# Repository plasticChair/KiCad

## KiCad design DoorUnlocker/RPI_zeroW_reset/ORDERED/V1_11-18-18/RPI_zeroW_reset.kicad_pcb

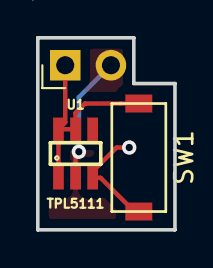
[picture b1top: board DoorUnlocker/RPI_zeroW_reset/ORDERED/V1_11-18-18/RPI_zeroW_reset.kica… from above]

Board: 2 copper layers, 7.6 x 10.7 mm, 4 parts (1 on the bottom side), 3 nets.

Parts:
J1: Conn_01x02; PinHeader_1x02_P2.54mm_Horizontal
R1: R; 1206
SW1: Button; Tact_SMD_Switch
U1: TPL5111; SOT-23-6

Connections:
unnamed: J1.1, SW1.2, U1.1, U1.5, U1.6
unnamed: J1.2, R1.1, U1.2
unnamed: R1.2, SW1.1, U1.3

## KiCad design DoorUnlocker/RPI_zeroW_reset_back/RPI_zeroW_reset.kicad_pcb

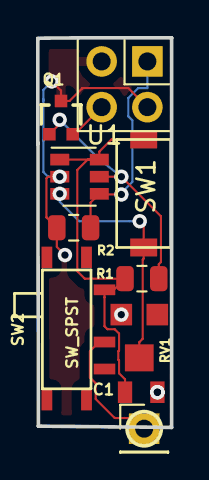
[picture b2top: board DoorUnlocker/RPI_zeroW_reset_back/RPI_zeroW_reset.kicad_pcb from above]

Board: 2 copper layers, 7.4 x 21.7 mm, 10 parts (0 on the bottom side), 7 nets.

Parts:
C1: C_Small; 0805
J1: RPI_Conn; PinHeader_2x02_P2.54mm_Vertical
J2: Conn_01x01; PinHeader_1x01_P2.54mm_Vertical
Q1: BSS83P; SOT323
R1, R2: R; R_0805_2012Metric
RV1: R_POT; Bourns_TC33X-2
SW1: SW_Push; Tact_SMD_Switch
SW2: SW_SPST; SWITCH_SPDT_PTH
U1: TPL5111; SOT-23-6

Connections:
+5V: C1.2, R1.2, SW1.2, SW2.1, U1.1, U1.6
/GPIO26: J1.1, R2.2, U1.4
/RUN: J1.4, Q1.2
GND: C1.1, J1.2, J1.3, Q1.3, R2.1, RV1.2, U1.2
unnamed: J2.1, SW2.2
unnamed: Q1.1, R1.1, U1.5
unnamed: RV1.1, SW1.1, U1.3

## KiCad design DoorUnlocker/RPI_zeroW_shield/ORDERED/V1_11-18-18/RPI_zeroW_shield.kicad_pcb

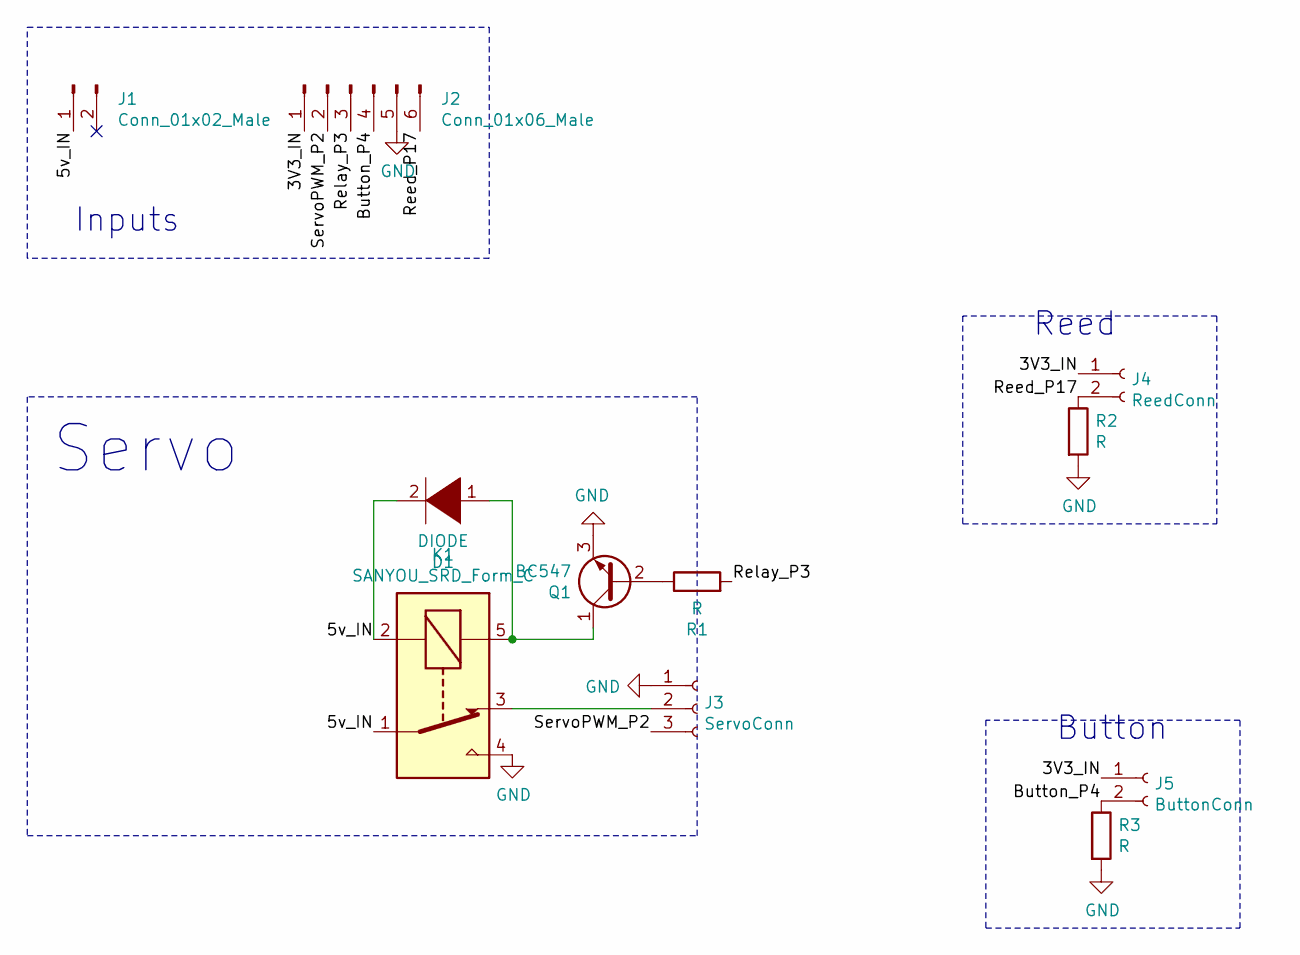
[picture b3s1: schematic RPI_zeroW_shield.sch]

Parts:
D1: DIODE; D_SOD-323_HandSoldering
J1: Conn_01x02_Male; PinHeader_1x02_P2.54mm_Horizontal
J2: Conn_01x06_Male; PinHeader_1x06_P2.54mm_Horizontal
J3: ServoConn; Pin_Header_1x03_Pitch2.54mm
J4: ReedConn; PinHeader_1x02_P2.54mm_Horizontal
J5: ButtonConn; PinHeader_1x02_P2.54mm_Horizontal
K1: SANYOU_SRD_Form_C; Relay_SPDT_SANYOU_SRD_Series_Form_C
Q1: BC547; TO-92_Inline
R1, R2, R3: R; 1206

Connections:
/3V3_IN: J2.1, J4.1, J5.1
/5v_IN: D1.2 (A), J1.1, K1.1, K1.2
/Button_P4: J2.4, J5.2, R3.1
/Reed_P17: J2.6, J4.2, R2.1
/Relay_P3: J2.3, R1.2
/ServoPWM_P2: J2.2, J3.3
GND: J2.5, J3.1, K1.4, Q1.3 (E), R2.2, R3.2
unnamed: D1.1 (K), K1.5, Q1.1 (C)
unnamed: J3.2, K1.3
unnamed: Q1.2 (B), R1.1

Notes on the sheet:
Servo
Button
Inputs
Reed

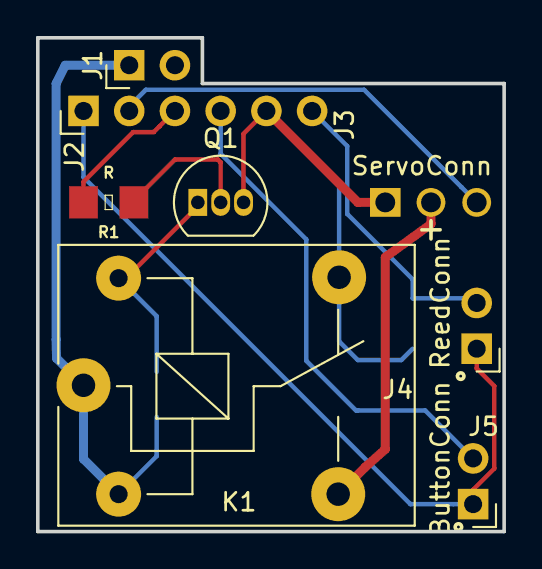
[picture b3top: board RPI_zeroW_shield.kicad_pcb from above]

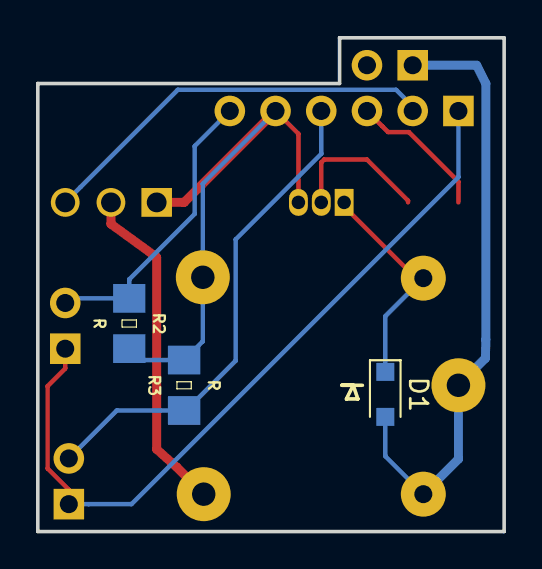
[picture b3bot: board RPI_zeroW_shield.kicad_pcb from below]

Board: 2 copper layers, 25.9 x 27.4 mm, 11 parts (3 on the bottom side), 10 nets.

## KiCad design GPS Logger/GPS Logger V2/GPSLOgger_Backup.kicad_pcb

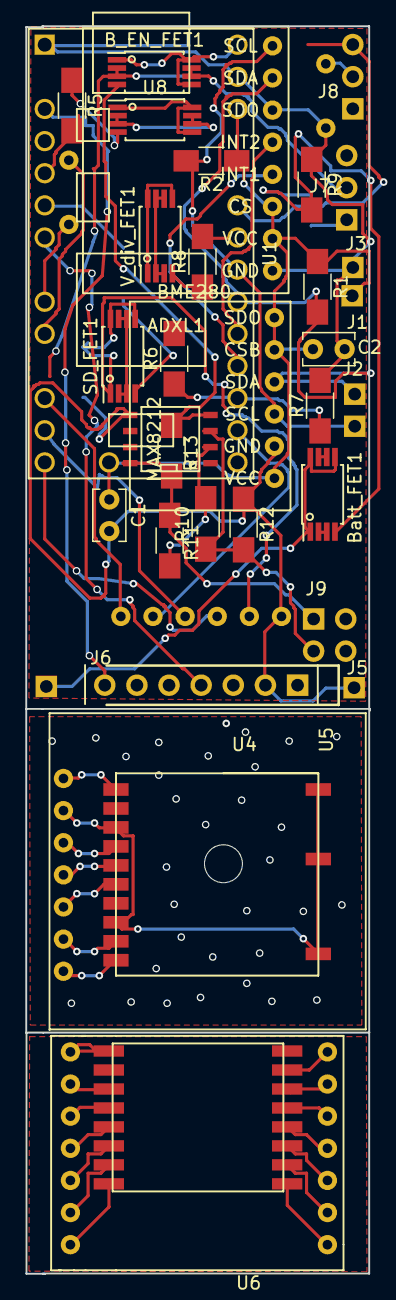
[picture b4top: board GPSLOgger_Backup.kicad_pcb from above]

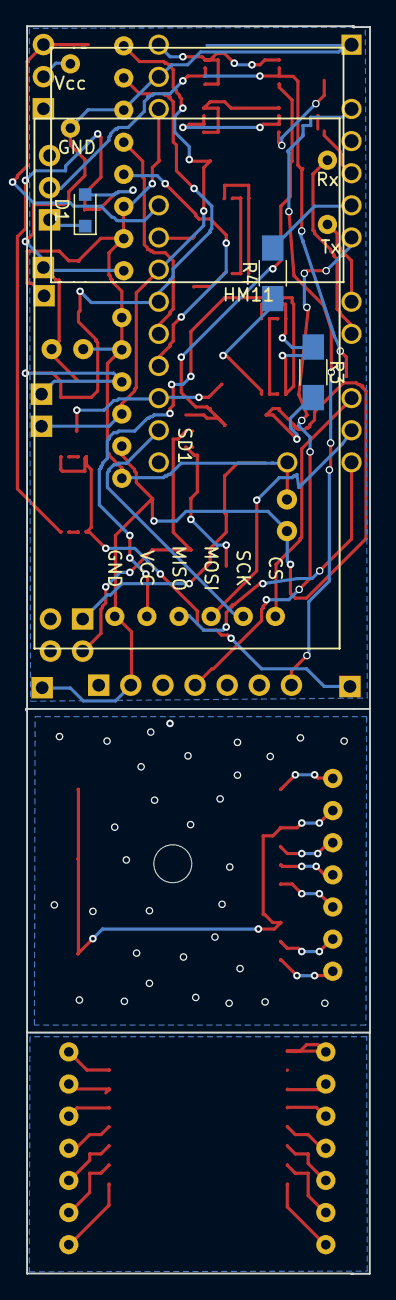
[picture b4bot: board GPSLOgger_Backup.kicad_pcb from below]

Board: 2 copper layers, 27.1 x 79.6 mm, 39 parts (5 on the bottom side), 33 nets.

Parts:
ADXL1: ADXL345_Breakout
BME280: BME280_Breakout
B_EN_FET1: Batt_En_FET; TSSOP-8_4.4x3mm_Pitch0.65mm_custom
Batt_FET1: Batt_EnFDW254p; TSSOP-8_4.4x3mm_Pitch0.65mm_custom
C1, C2: C; C_Rect_L4.0mm_W2.5mm_P2.50mm
D1: D_Schottky; D_SOD-323_HandSoldering
HM11: HM-11_BreakConns
J1: 3.3V; Pin_Header_1x01_Pitch2.54mm
J2: SDA; Pin_Header_1x01_Pitch2.54mm
J3: GND; Pin_Header_1x01_Pitch2.54mm
J4: SDL; Pin_Header_1x01_Pitch2.54mm
J5: -Batt; Pin_Header_1x01_Pitch2.54mm
J6: +Batt; Pin_Header_1x01_Pitch2.54mm
J7: BattSwitch; Pin_Header_1x03_Pitch2.54mm
J8: HM11Switch; Pin_Header_1x03_Pitch2.54mm
J9: CONN_02X02; Pin_Header_Angled_2x02_Pitch2.54mm
MAX8212: MAX8212; SOIC-8-N
R1, R2, R6, R7: R; R_1206_HandSoldering
R3, R4, R5: R_Small; R_1206_HandSoldering
R8: 10k; R_1206_HandSoldering
R9: 100k; R_1206_HandSoldering
R10, R11, R12, R13: 1M; R_1206_HandSoldering
SD1: SDCard_Breakout
SD_FET1: SD_EN_FDW254p; TSSOP-8_4.4x3mm_Pitch0.65mm_custom
U1: Teensy-LC; Teensy_LC
U4: GNS601_Breakout
U5: GPS Connector; Pin_Header_Angled_1x07_Pitch2.54mm
U6: HM-11; HM-11_Breakout
U8: GPS_FDW254p; TSSOP-8_4.4x3mm_Pitch0.65mm_custom
V_div_FET1: VDiv_FDW254p; TSSOP-8_4.4x3mm_Pitch0.65mm_custom

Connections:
+3V3: ADXL1.2, ADXL1.3, BME280.1, BME280.2, BME280.6, C1.1, C2.1, J1.1, R1.1, R2.1, U1.16, U1.31
GND: ADXL1.1, ADXL1.6, BME280.5, C1.2, C2.2, HM11.12, J3.1, J5.1, MAX8212.5, R3.2, R7.2, R9.1, R12.1, SD1.1, U1.1, U5.2
unnamed: ADXL1.4, U1.23
unnamed: ADXL1.5, U1.24
unnamed: ADXL1.7, BME280.3, J2.1, R1.2, U1.25
unnamed: ADXL1.8, BME280.4, J4.1, R2.2, U1.26
unnamed: B_EN_FET1.1, U1.33
unnamed: B_EN_FET1.2, J7.2, J9.1, MAX8212.8, R11.2, R13.2
unnamed: B_EN_FET1.4, MAX8212.4, R13.1
unnamed: Batt_FET1.1, J6.1
unnamed: Batt_FET1.2, D1.1, J7.1
unnamed: Batt_FET1.4, D1.2, R9.2
unnamed: HM11.2, U1.9
unnamed: HM11.4, U1.10
unnamed: HM11.9, J8.2
unnamed: J8.3, U1.28
unnamed: J9.3, MAX8212.3, R10.1, R12.2
unnamed: MAX8212.2, R10.2, R11.1
unnamed: R3.1, SD1.2, SD_FET1.1
unnamed: R4.1, SD_FET1.4
unnamed: R4.2, U1.6
unnamed: R5.1, U8.4
unnamed: R5.2, U1.5
unnamed: R6.1, R7.1, U1.22
unnamed: R8.1, V_div_FET1.4
unnamed: R8.2, U1.27
unnamed: SD1.3, U1.14
unnamed: SD1.4, U1.13
unnamed: SD1.5, U1.21
unnamed: SD1.6, U1.12
unnamed: U1.3, U5.7
unnamed: U1.7, U5.4
unnamed: U4.3, U4.8, U4.11, U4.12, U4.13

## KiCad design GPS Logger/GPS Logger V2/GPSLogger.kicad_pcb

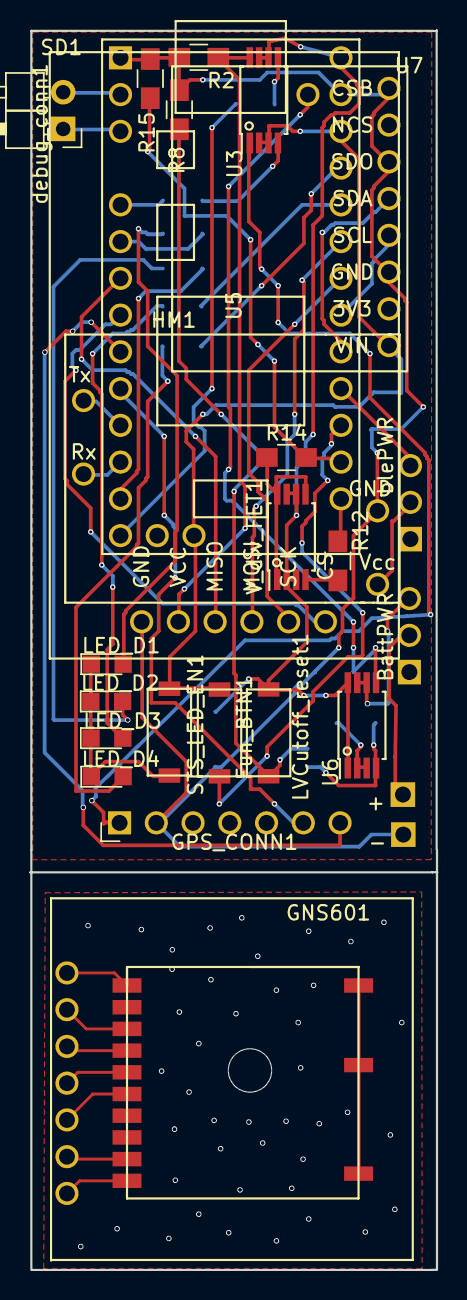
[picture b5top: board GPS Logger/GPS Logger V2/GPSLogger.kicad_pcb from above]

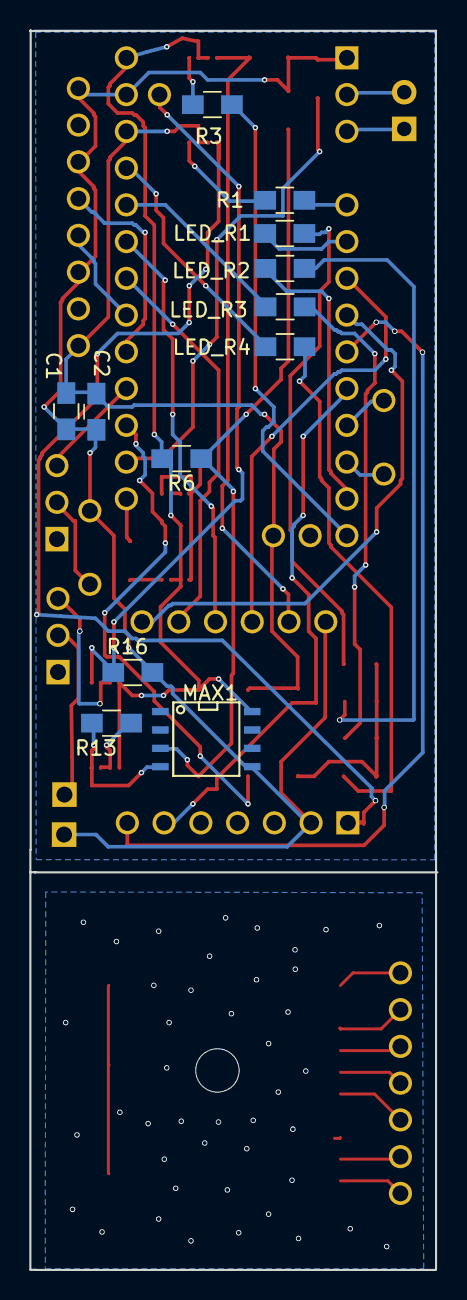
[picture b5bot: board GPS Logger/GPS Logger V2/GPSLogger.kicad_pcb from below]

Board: 2 copper layers, 28.0 x 85.7 mm, 38 parts (12 on the bottom side), 44 nets.

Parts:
+: +Batt; Pin_Header_1x01_Pitch2.54mm
-: -Batt; Pin_Header_1x01_Pitch2.54mm
BattPWR: BattSwitch; Pin_Header_1x03_Pitch2.54mm
C1, C2: C; C_0805_HandSoldering
Fun_BTN1: Fun_BTN; SMD_Switch_3x6
GNS601: GNS601_Breakout
GPS_CONN1: GPS Connector; Pin_Header_Angled_1x07_Pitch2.54mm
HM1: HM-11_BreakConns
LED_D1, LED_D2, LED_D3, LED_D4: LED; LED_0805
LED_R1, LED_R2, LED_R3, LED_R4: XXk; R_0805_HandSoldering
LVCutoff_reset1: LVCutoff_reset; SMD_Switch_3x6
MAX1: MAX8212; SOIC-8-N
R1, R3, R12: 10k; R_0805_HandSoldering
R2, R6, R16: 100k; R_0805_HandSoldering
R8: 56k; R_0805_HandSoldering
R13: 1M; R_0805_HandSoldering
R14: 22k; R_0805_HandSoldering
R15: 68k; R_0805_HandSoldering
SD1: SDCard_Breakout
STS_LED_EN1: STS_LED_EN; SMD_Switch_3x6
U3, U6: Si6943DQ; TSSOP-8_4.4x3mm_Pitch0.65mm_custom
U5: Teensy-LC; Teensy_LC
U7: GY-91
V_div_FET1: VDiv_FDW254p; TSSOP-8_4.4x3mm_Pitch0.65mm_custom
blePWR: BLE_PWR_Switch; Pin_Header_1x03_Pitch2.54mm
debug_conn1: debug_conn; Pin_Header_Angled_1x02_Pitch2.54mm

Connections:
+3V3: C1.1, C2.1, Fun_BTN1.2, STS_LED_EN1.2, U3.2, U3.3, U5.16, U5.31, U7.1
+BATT: LVCutoff_reset1.1, MAX1.8, R6.2, U3.6, U3.7, U5.33, U6.1, U6.8, V_div_FET1.2, V_div_FET1.3, V_div_FET1.6, V_div_FET1.7
GND: -.1, C1.2, C2.2, GPS_CONN1.2, HM1.12, MAX1.5, R2.2, R8.1, R15.2, R16.1, SD1.1, U5.1, U5.32, U7.3, U7.6, U7.8
unnamed: HM1.9, blePWR.2
unnamed: U5.24, blePWR.3
unnamed: +.1, BattPWR.2
unnamed: BattPWR.3, U6.6, U6.7
unnamed: Fun_BTN1.1, U5.23
unnamed: GPS_CONN1.1, U3.1
unnamed: GPS_CONN1.6, U5.10
unnamed: GPS_CONN1.7, U5.9
unnamed: HM1.2, U5.11
unnamed: HM1.4, U5.12
unnamed: LED_D1.1, LED_D2.1, LED_D3.1, LED_D4.1, STS_LED_EN1.1
unnamed: LED_D1.2, LED_R1.1
unnamed: LED_D2.2, LED_R2.1
unnamed: LED_D3.2, LED_R3.1
unnamed: LED_D4.2, LED_R4.1
unnamed: LED_R1.2, U5.6
unnamed: LED_R2.2, U5.13
unnamed: LED_R3.2, U5.29
unnamed: LED_R4.2, U5.30
unnamed: LVCutoff_reset1.2, MAX1.3, R6.1, R8.2
unnamed: MAX1.4, R13.1, U6.4
unnamed: R1.1, U3.4
unnamed: R1.2, U5.5
unnamed: R2.1, SD1.2, U3.8
unnamed: R3.1, U5.14
unnamed: R3.2, U3.5
unnamed: R12.1, V_div_FET1.4
unnamed: R12.2, U5.21
unnamed: R13.2, U6.2, U6.3
unnamed: R14.1, V_div_FET1.1, V_div_FET1.5, V_div_FET1.8
unnamed: R14.2, R15.1, U5.22
unnamed: R16.2, U5.34, U6.5
unnamed: SD1.3, U5.7
unnamed: SD1.4, U5.28
unnamed: SD1.5, U5.27
unnamed: SD1.6, U5.8
unnamed: GNS601.3, GNS601.8, GNS601.11, GNS601.12, GNS601.13
unnamed: U5.2, debug_conn1.2
unnamed: U5.3, debug_conn1.1
unnamed: U5.25, U7.5
unnamed: U5.26, U7.4

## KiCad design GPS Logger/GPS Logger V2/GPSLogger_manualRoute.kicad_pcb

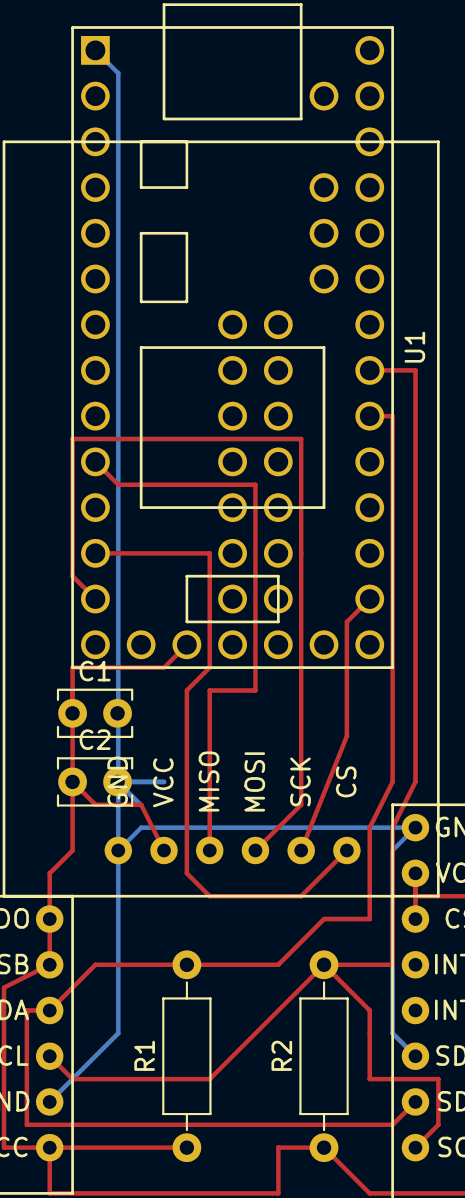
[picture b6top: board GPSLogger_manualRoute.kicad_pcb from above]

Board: 2 copper layers, 8 parts (0 on the bottom side), 8 nets.

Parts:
C1, C2: C; C_Rect_L4.0mm_W2.5mm_P2.50mm
R1, R2: R; R_Axial_DIN0207_L6.3mm_D2.5mm_P10.16mm_Horizontal
U1: Teensy-LC; Teensy30_31_32_LC
U2: BME280_Breakout
U3: SDCard_Breakout
_3: ADXL345_Breakout

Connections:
+3V3: C1.1, C2.1, R1.1, R2.1, U1.16, U2.1, U2.2, U2.6, U3.2, _3.2, _3.3
GND: C1.2, C2.2, U1.1, U2.5, U3.1, _3.1, _3.6
unnamed: R1.2, U1.25, U2.3, _3.7
unnamed: R2.2, U1.26, U2.4, _3.8
unnamed: U1.10, U3.3
unnamed: U1.12, U3.6
unnamed: U1.13, U3.4
unnamed: U1.21, U3.5

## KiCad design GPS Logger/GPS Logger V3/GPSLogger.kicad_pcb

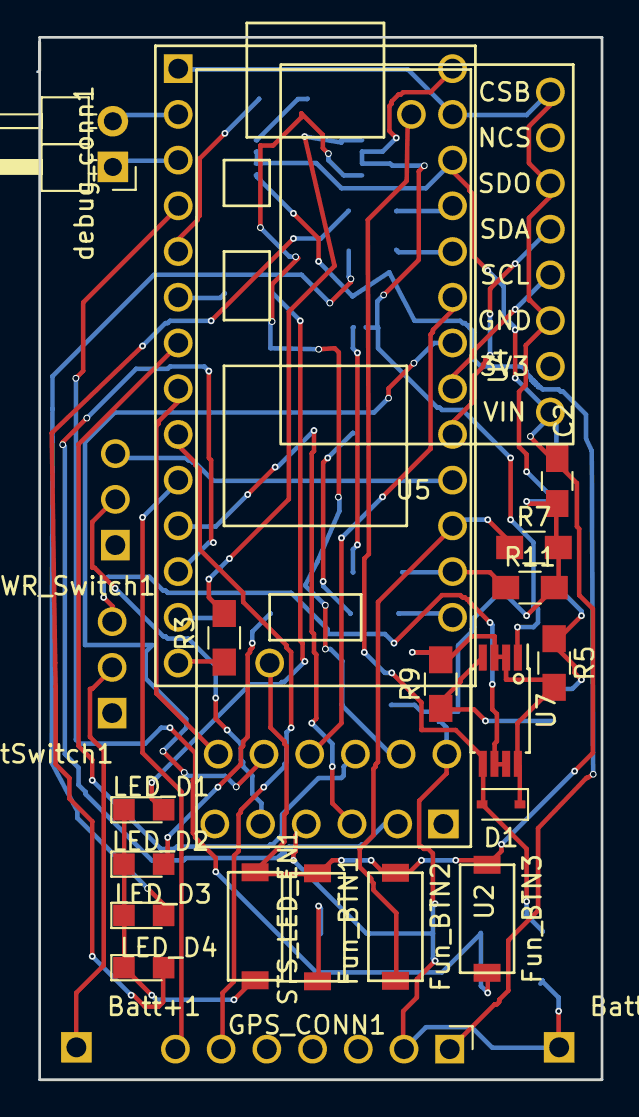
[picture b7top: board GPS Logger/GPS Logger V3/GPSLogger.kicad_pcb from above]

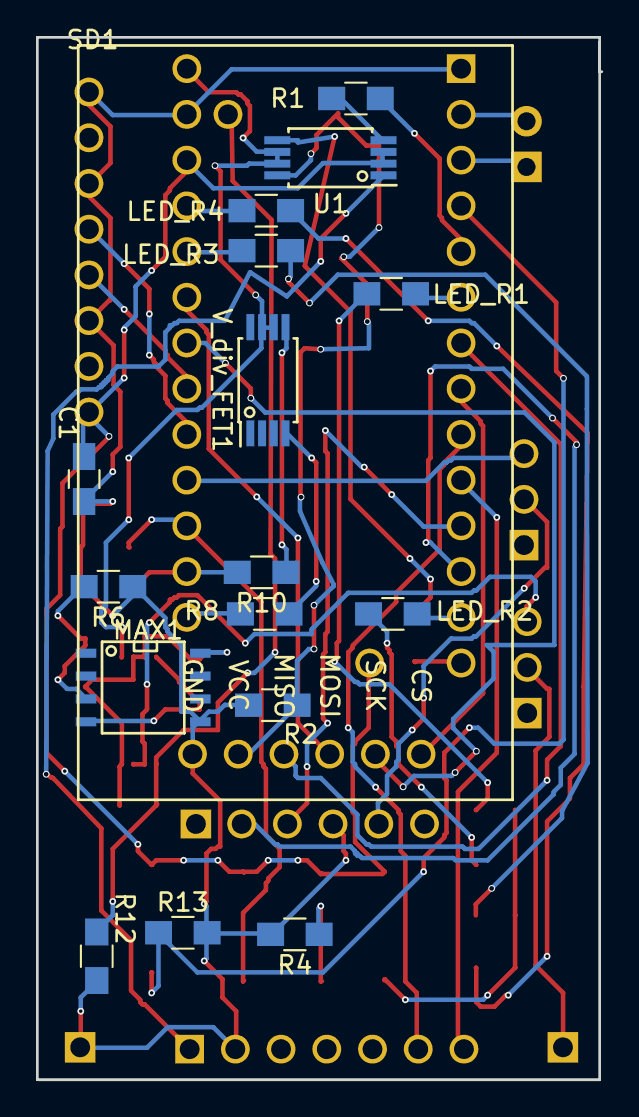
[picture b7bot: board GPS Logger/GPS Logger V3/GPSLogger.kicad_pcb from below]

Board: 2 copper layers, 31.4 x 57.9 mm, 42 parts (17 on the bottom side), 45 nets.

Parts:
BLE_PWR_Switch1: BLE_PWR_Switch; Pin_Header_1x03_Pitch2.54mm
Batt+1: +Batt; Pin_Header_1x01_Pitch2.54mm
Batt-1: -Batt; Pin_Header_1x01_Pitch2.54mm
BattSwitch1: BattSwitch; Pin_Header_1x03_Pitch2.54mm
C1: 82nF; C_0805_HandSoldering
C2: 2.2uF; C_0805_HandSoldering
D1: D; D_SOD-323
Fun_BTN1, Fun_BTN3: LVCutoff_reset; SMD_Switch_3x6
Fun_BTN2: Fun_BTN; SMD_Switch_3x6
GPS_CONN1: GPS Connector; Pin_Header_Angled_1x07_Pitch2.54mm
LED_D1: BLUE; LED_0805
LED_D2: GREEN; LED_0805
LED_D3: RED; LED_0805
LED_D4: ORANGE; LED_0805
LED_R1: 5.6; R_0805_HandSoldering
LED_R2: 10; R_0805_HandSoldering
LED_R3, LED_R4: 56; R_0805_HandSoldering
MAX1: MAX8212; SOIC-8-N
R1, R3, R4, R7, R8, R13: 10k; R_0805_HandSoldering
R2, R5, R12: 100k; R_0805_HandSoldering
R6: 56k; R_0805_HandSoldering
R9: 1M; R_0805_HandSoldering
R10: 82k; R_0805_HandSoldering
R11: 22k; R_0805_HandSoldering
SD1: SDCard_Breakout
STS_LED_EN1: STS_LED_EN; SMD_Switch_3x6
U1, U7: Si6943DQ; TSSOP-8_4.4x3mm_Pitch0.65mm_custom
U2: BLE_module; HM-10_breakout
U4: Teensy-LC; Teensy_LC
U5: GY-91
V_div_FET1: VDiv_FDW254p; TSSOP-8_4.4x3mm_Pitch0.65mm_custom
debug_conn1: debug_conn; Pin_Header_Angled_1x02_Pitch2.54mm

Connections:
+3V3: C1.1, C2.1, Fun_BTN1.2, Fun_BTN2.2, Fun_BTN3.2, STS_LED_EN1.2, U1.2, U1.3, U4.16, U4.31, U5.1
+BATT: U1.6, U1.7, U4.33, U7.1, V_div_FET1.6, V_div_FET1.7
/BattPostSwitch: D1.1, MAX1.8, R5.2, R9.2, U7.2, U7.3, U7.8
/USBPower+: D1.2, R12.2, U4.34, U7.5
GND: Batt-1.1, C1.2, C2.2, GPS_CONN1.2, MAX1.5, R2.2, R4.2, R6.1, R7.2, R11.2, R12.1, R13.2, SD1.1, U2.4, U4.1, U4.32, U5.3, U5.6, U5.8
unnamed: BLE_PWR_Switch1.2, U2.5
unnamed: BLE_PWR_Switch1.3, U4.24
unnamed: Batt+1.1, BattSwitch1.2
unnamed: BattSwitch1.3, U7.6, U7.7
unnamed: Fun_BTN1.1, R4.1
unnamed: Fun_BTN2.1, R7.1, U4.23
unnamed: Fun_BTN3.1, R13.1, U4.4
unnamed: GPS_CONN1.1, U1.1
unnamed: GPS_CONN1.6, U4.9
unnamed: GPS_CONN1.7, U4.10
unnamed: LED_D1.1, LED_D2.1, LED_D3.1, LED_D4.1, STS_LED_EN1.1
unnamed: LED_D1.2, LED_R1.1
unnamed: LED_D2.2, LED_R2.1
unnamed: LED_D3.2, LED_R3.1
unnamed: LED_D4.2, LED_R4.1
unnamed: LED_R1.2, U4.6
unnamed: LED_R2.2, U4.13
unnamed: LED_R3.2, U4.29
unnamed: LED_R4.2, U4.30
unnamed: MAX1.3, R5.1, R6.2
unnamed: MAX1.4, R9.1, U7.4
unnamed: R1.1, U1.4
unnamed: R1.2, U4.5
unnamed: R2.1, SD1.2, U1.8
unnamed: R3.1, U4.14
unnamed: R3.2, U1.5
unnamed: R8.1, V_div_FET1.4
unnamed: R8.2, U4.21
unnamed: R10.1, V_div_FET1.5
unnamed: R10.2, R11.1, U4.22
unnamed: SD1.3, U4.7
unnamed: SD1.4, U4.28
unnamed: SD1.5, U4.27
unnamed: SD1.6, U4.8
unnamed: U2.2, U4.12
unnamed: U2.3, U4.11
unnamed: U4.2, debug_conn1.2
unnamed: U4.3, debug_conn1.1
unnamed: U4.25, U5.5
unnamed: U4.26, U5.4
